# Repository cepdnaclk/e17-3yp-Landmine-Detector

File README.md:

---
layout: home
permalink: index.html

repository-name: e17-3yp-Landmine-Detector 
title: Landmine Detector 
---

[comment]: # "This is the standard layout for the project, but you can clean this and use your own template"

# Landmine Detector 

## Table of Contents
* [Problem Overview](#Problem-Overview)
* [Existing System](#Existing-System)
* [Proposed System](#Proposed-System)
* [Key Features and Scope](#Key-Features-and-Scope)
* [Hardware](https://github.com/Akilax0/e17-3yp-Landmine-Detector/tree/main/_designs/hardware)
* [Cloud Architecture](https://github.com/Akilax0/e17-3yp-Landmine-Detector/tree/main/_designs/cloud_archiecture)
* [Database Design](https://github.com/Akilax0/e17-3yp-Landmine-Detector/tree/main/_designs/database_schemas)
* [Team](#Team)
* [Links](#Links)

## Problem Overview

In a world where there is an abundance of weapons there is a need to provide security to the armed personnel and also people living in war prone areas is of the utmost importance.     

A Landmine is basically an explosive device hidden underground by the enemy and explodes when any personnel or vehicle steps or drives over it. The Pressure created by the personnel or the vehicle on the ground below which the mine is laid acts as the detonator for the mine explosion. 

The damage caused by the Landmine explosion is fatal and hence detecting landmines becomes necessary before the army personnel or vehicle accidentally steps over it. The major challenge is detecting these landmines without causing any explosion and diffusing them once they are detected.

The process of detecting landmines is technically termed as minesweeping and process of removing or defusing the mines is known as demining or mine clearance. Minesweeping was earlier done using trained animals like dogs and rats but modern methods includes metal detectors and various tooled attached to the vehicles. But any manual intervention of a human is always dangerous.

## Existing System

Robots are used for various applications in industrial area. Robot performs various activities and is becoming more advanced. Thats the reason nowadays Landmine Detection Robotic Vehicles and unmanned robots are used to detect the landmines. Robots are always reliable in terms of perfection in detection and no human life is endangered in the process. An automatic robot, which is capable of detecting buried landmines and taking from their locations, while enabling the operator to control the robot wirelessly from a distance. 

<!-- GPR has been considered as the most promising subsurface sensing technique for landmine clearance operations in combination with a metal detector. This is because of its ability to detect both metallic and nonmetallic landmines. Furthermore, the capability for imaging and post processing of data enables the identification of detected objects. A system combining GPR and a metal detector is commonly called a dual sensor. The system uses the metal detector as the primary sensor for the detection and localization of metal-containing objects, after which it switches to GPR as the secondary sensor for target identification. GPR for landmine detection commonly employs relatively high frequencies in order to detect and/or image small objects near the surface and also to reduce the size of the antennas for easier handling and higher mobility. With high frequencies, GPR becomes more sensitive to the heterogeneity of the media surrounding the object, which results in unwanted scattering in the data. The unwanted scattered waves are commonly referred to as clutter. Clutter degrades the quality of the GPR data and makes their analysis and interpretation difficult. In the case of landmine detection, a false analysis or interpretation of the data may lead to an accidental detonation -->

## Proposed System
A system which involves a user interface , server and a robot to detect Landmines in a given area autonomously.
The Landmine detecting robots are designed to cover maximum possible area of landmine field for detection of landmines. The detected landmines along with scanned and leftover area are represented on a visual map.
The whole set of tasks are designed to be done with minimum human interactions making it safer and at the same time more efficient.

## Key Features and Scope
- Automated path finding
- GPS based navigation
- Landmine detection using Pulse Induction
- Visualization of data as an overlay on maps
- Scalability for multiple bots

For more information about the project please checkout our projects page at 
[Project Page](https://cepdnaclk.github.io/e17-3yp-Landmine-Detector)

---

## Team
-  E/17/154, KARUNANAYAKE A.I, [e17154@eng.pdn.ac.lk](mailto:name@email.com)
-  E/17/297, RUPASINGHE T.T.V.N., [e17297@eng.pdn.ac.lk](mailto:name@email.com)
-  E/17/206, MANOHARA H.T., [e17206@eng.pdn.ac.lk](mailto:name@email.com)

## Links
<!-- - [Project Page](https://cepdnaclk.github.io/e17-3yp-Le-Detector) -->
- [Project Repository](https://github.com/cepdnaclk/e17-3yp-Landmine-Detector)
- [Department of Computer Engineering](http://www.ce.pdn.ac.lk/)
- [University of Peradeniya](https://eng.pdn.ac.lk/)

[//]: # (Please refer this to learn more about Markdown syntax)
[//]: # (https://github.com/adam-p/markdown-here/wiki/Markdown-Cheatsheet)

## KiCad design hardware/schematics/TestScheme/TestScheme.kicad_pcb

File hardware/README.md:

# Hardware Modules

## Motor Controls

### Parts

- L298N Motor Driver
- Motors
- Wheels
- Atmega328p
- 22pF capacitors
- 10microF capacitor
- Lipo battery 
- Ultrasonic sensors
- rotary sensor

### Schematics

## Main Board

## Metal Detector

## Communication 

## Power Supply

## Chassis

##

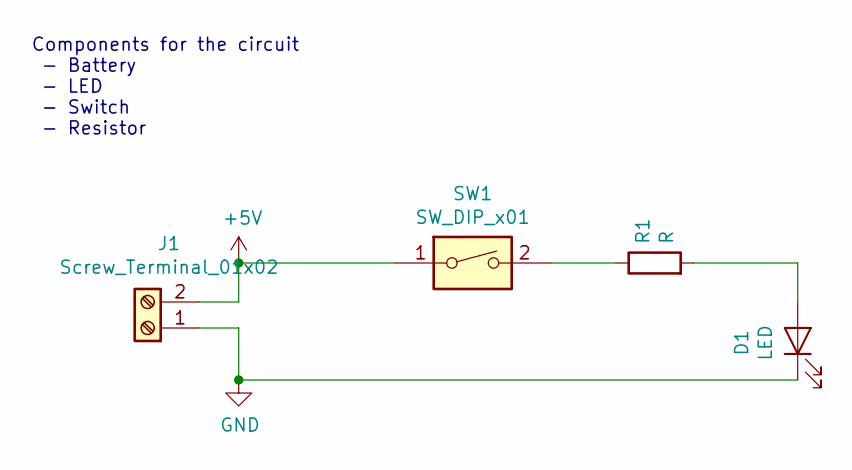
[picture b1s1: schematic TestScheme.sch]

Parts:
D1: LED
J1: Screw_Terminal_01x02
R1: R
SW1: SW_DIP_x01

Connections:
+5V: J1.2, SW1.1
GND: D1.1 (K), J1.1
unnamed: D1.2 (A), R1.2
unnamed: R1.1, SW1.2

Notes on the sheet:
Components for the circuit - Battery - LED - Switch - Resistor

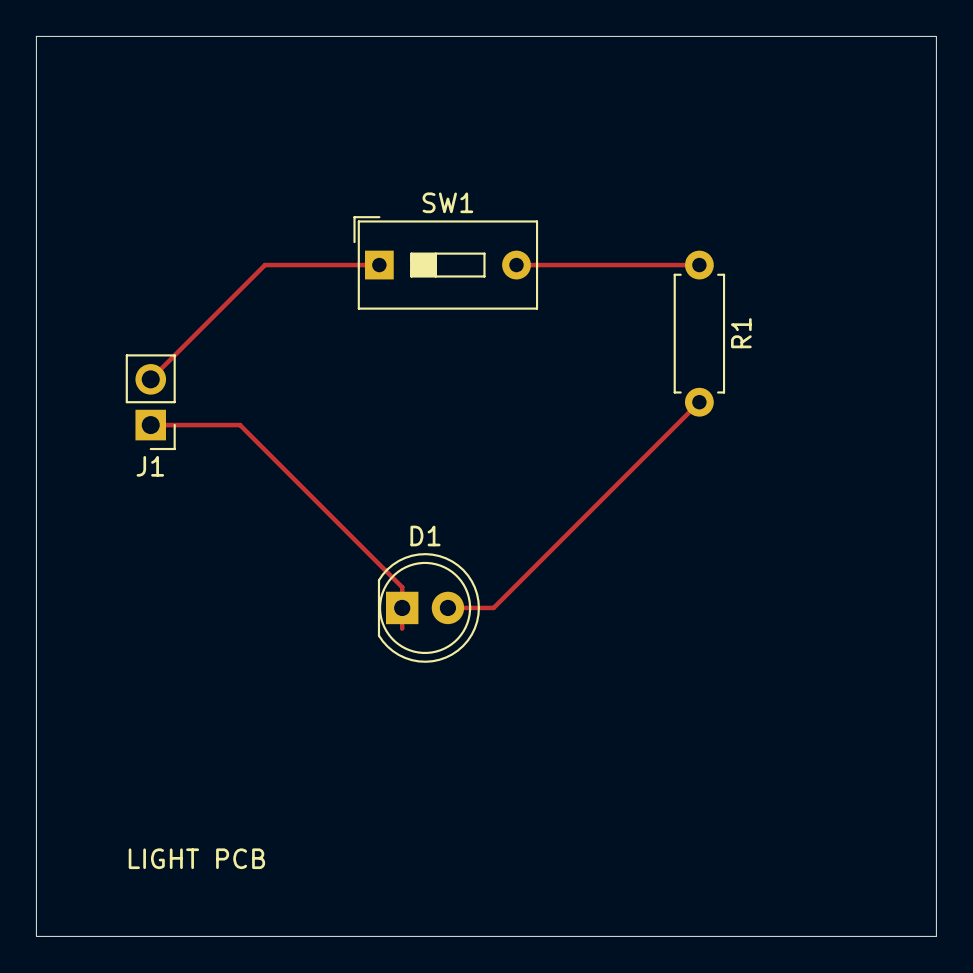
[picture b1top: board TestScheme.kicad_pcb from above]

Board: 2 copper layers, 50.0 x 50.0 mm, 4 parts (0 on the bottom side), 4 nets.

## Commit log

2021-06-29 index.json
2021-06-29 web_updates
2021-06-30 SIM900A_init
2021-07-01 Team page started, Images and logos added
2021-07-01 Images added to the Team page
2021-07-08 website_updates
2021-07-09 web updates
2021-07-10 logo.png
2021-07-11 Add Intro,problem and solution to the website
2021-07-11 Links added
2021-07-11 into updates
2021-07-14 Font-style changed
2021-07-14 Logo added
2021-07-14 Images updated
2021-07-17 Added github logos. Removed FB
2021-07-17 Header added
2021-07-18 Topic added
2021-07-21 Create webapp
2021-07-21 Initiate frontend webUI
2021-07-21 rm Web-UI
2021-07-21 add test loging
2021-07-21 webapp push
2021-07-26 database_init
2021-07-26 README.md updates
2021-07-27 README.md update
2021-07-27 hardware_schematics
2021-07-29 scripts_simm900A
2021-07-29 database_updates
2021-07-30 web_ha
2021-07-30 Solution Architecture change
2021-07-30 add logos to solution architecture
2021-07-30 add update to solution architecture ddk
2021-07-31 change the text allignment in solution architecture
2021-07-31 # columns added to the footer
2021-07-31 Updated footer
2021-07-31 Footer done
2021-07-31 timeline_init
2021-07-31 small_web_update
2021-07-31 add budget compoenent
2021-07-31 add a table and data
2021-07-31 add changes to css
2021-07-31 change size of rows
2021-07-31 add changes to design
2021-07-31 add hover effect
2021-07-31 Contacts added
2021-08-01 web UI
2021-08-01 small_updates
2021-08-01 sol_architecture
2021-08-01 add security title
2021-08-01 add cloud security
2021-08-01 add basic iot security
2021-08-01 add changes
2021-08-01 Robo-design added
2021-08-03 database
2021-08-04 database_schema
2021-08-05 database_schemas
2021-08-06 configs
2021-08-06 iot_connect
2021-08-07 simulation
2021-08-08 visualizer_setup
2021-08-09 simu_updates
2021-08-10 simu_plane
2021-08-13 wsl changes
2021-08-14 start on cloud architect design
2021-08-14 add readme
2021-08-15 org_updates
2021-08-15 cloud_schema
2021-08-15 simulation restore
2021-08-17 hardware _designs
2021-08-19 schemas
2021-08-19 hardware_designs
2021-08-27 webUI designs
2021-08-30 esp32 testscripts
2021-09-01 Create Video
2021-09-01 added video
2021-09-02 First image of the state diagram is attached
2021-09-02 Navbar CSS updated
2021-09-02 Second image of the state diagram is attached
2021-09-03 Budget updated
2021-09-03 hardware_designs_website
2021-09-03 Add cloud architecture and UI images
2021-09-03 ER diagram added
2021-09-03 Relational schema added
2021-09-03 Cloud architecture edited
2021-09-03 hardware_updates
2021-09-07 ESP32 testing
2021-09-08 Re-Initatilizing WebApp
2021-09-11 Created Authentication flow
2021-09-11 signin UI
2021-09-11 remove amplify-backup
2021-09-11 remove_ESP build files
2021-09-16 aws backend delete
2021-09-16 aws_backend_test
2021-09-16 aws_backend
2021-09-16 aws_api
2021-09-17 api_init
2021-09-17 aws_api_init
2021-09-18 viualizer grid
2021-09-20 Sidebar low level started
2021-09-20 Profile page started
2021-09-23 Map added v1
2021-09-23 Map added v2
2021-09-23 Map added v3
2021-09-24 test models
2021-09-24 remove 3d
2021-09-24 Leaflet css added to index.html
2021-09-24 OpenStreetMap created v1
2021-09-24 Unexpected token error fixed
2021-09-24 Map works but not visible
2021-09-24 Map added but marker is not working
2021-10-03 Marker works now
2021-10-03 Map updates
2021-10-11 UseStates added to the marker
2021-10-11 Popup added
2021-10-11 Circle added
2021-10-11 API add
2021-10-11 small update
2021-10-11 functional component of openstreet
2021-10-13 Testing page created
2021-10-13 Add new UI images UI slideshow
2021-10-13 Add new video
2021-10-14 API schema change
2021-10-14 Map is somewhat ok now
2021-10-14 wroom docs added
2021-10-15 schema change
2021-10-15 Routes added
2021-10-15 All routers added
2021-10-16 change buttons and input boxes in profile page
2021-10-16 WebApp intergration v1.0
2021-10-16 Input boxes ok, data sending ok
2021-10-16 History page OK
2021-10-16 sfml setup
2021-10-18 lambda trigger
2021-10-18 Files fixed
2021-10-18 Area of a circle ok
2021-10-19 add some updates to UI
2021-10-19 CSS chnaged
2021-10-19 Lat Lan changed
2021-10-19 OpenStreet new css
2021-10-19 Lan/Lat problem fixed
2021-10-19 Sample second point is ok
2021-10-19 Multiple markers Ok
2021-10-20 lambda robot status
2021-10-21 redo RobotStatus
2021-10-21 Area identified. Array created
2021-10-21 Map data store
2021-10-21 rearrange Data
2021-10-21 org model
2021-10-21 change color theme of login UI
2021-10-21 Data to Webapp
2021-10-21 Robot User : ID
2021-10-21 change routes
2021-10-21 Cretae data function and got id from aws
2021-10-22 Profile somewhat ok
2021-10-22 start with profile page and some changes in UI
2021-10-22 Add user greeting on top
2021-10-22 Coordinates problem solved
2021-10-22 Signout button customized
2021-10-23 New updates
2021-10-23 Initial create search bug fixed
2021-10-23 Created a HTTP API to get robotable
2021-10-23 Set Labels
2021-10-23 Input box validation
2021-10-23 Signout custom button fixed
2021-10-23 Map css updated
2021-10-23 Clearing option cleared
2021-10-23 Change Password component added
2021-10-23 show user data in profile page
2021-10-23 Robot names got
2021-10-23 Status also included
2021-10-24 Floating number problem solved
2021-10-24 Table Ok ver 1
2021-10-24 Coordinates table done
2021-10-24 Colours assigned for robots
2021-10-24 selenium testing
2021-10-24 Schema Graph
2021-10-24 Copied robot details to openstreet
2021-10-24 History created
2021-10-24 Css updated
2021-10-24 White space problem solved in text boxes
2021-10-24 coordinates table updated
2021-10-25 changed the colors of robo status and removed status from profile
2021-10-25 changed the favcon
2021-10-25 add new UI images to website
2021-10-25 Added 3 columns
2021-10-25 FAQ created
2021-10-25 History theme changed
2021-10-25 Task ok
2021-10-25 Testing
2021-11-22 test script
2021-11-24 test schematics
2021-11-26 motor implementation
2021-11-26 Motor Driver AVR
2021-11-28 Motor Driver Schematics
2021-12-07 Motor Driver init
2021-12-11 hardware start
2021-12-12 schematic mainboard satart
2021-12-12 motor controls
2021-12-12 i2c esp to atmel
2021-12-12 MPU start
2021-12-15 mpu-esp32 init
2021-12-17 esp uart config
2021-12-18 new website
2021-12-18 rm new_website folder
2021-12-18 herosection define
2021-12-18 cards
2021-12-20 Cards added
2021-12-21 new website interface
2021-12-23 main board decisionns
2021-12-23 GPS NMEA data to ESP32
2021-12-23 gazebo init
2021-12-26 parallel tasks
2022-01-03 new website introduction
2022-10-22 Bluetooth controller app initialied
2022-10-30 obstacle detection
2022-11-12 bluetooth, wifi, AWS
2022-11-12 gps data to arduino over i2c
2022-11-12 platformio Communication unit
2022-11-12 obstacle distance
2022-11-15 Simple api for robot created
2022-11-15 hardware updates
2022-11-15 Mqtt with flask
2022-11-15 Lat and lon ok
2022-11-16 Connected with heroku
2022-11-16 Add interval to showlandmines function
2022-11-16 All detected landmines are displayed
2022-11-16 Only detected landmines are displayed in the map
2022-11-16 code divided into tasks
2022-11-17 Working for obstacles
2022-11-17 All landmines and obstacles are displayed
2022-11-17 API bug fixed
2022-11-17 Add dependancies
2022-11-18 motor control init
2022-11-19 favicon and title changed
2022-11-19 3d model added
2022-11-19 bluetooth controller UI added
2022-11-19 Autonomous drive v1
2022-11-20 Main unit updates
2022-11-20 Added post
2022-11-20 Create coodinate function works in backend
2022-11-20 Post method works
2022-11-20 Mqtt can be published when creating a search
2022-11-20 Coordinates are pulished through mqtt
2022-11-20 Can identify the waypoints
2022-11-20 Can identify the finish
2022-11-20 Added the endpoint
2022-11-20 Robot name added
2022-11-20 Endpoint changed
2022-11-21 MQTT changed and data format changed
2022-11-21 manual controller testing video added
2022-11-21 timeline updated
2022-11-21 Coordinates calculation rounded
2022-11-21 hardware setup
2022-11-22 waypoint navigation
2022-11-22 Coordinates changed
2022-11-24 Unit testing added
2022-11-24 Added PCB designs
2022-11-24 Added power designs
2022-11-24 Added competitions
2022-11-24 Updated hardware
